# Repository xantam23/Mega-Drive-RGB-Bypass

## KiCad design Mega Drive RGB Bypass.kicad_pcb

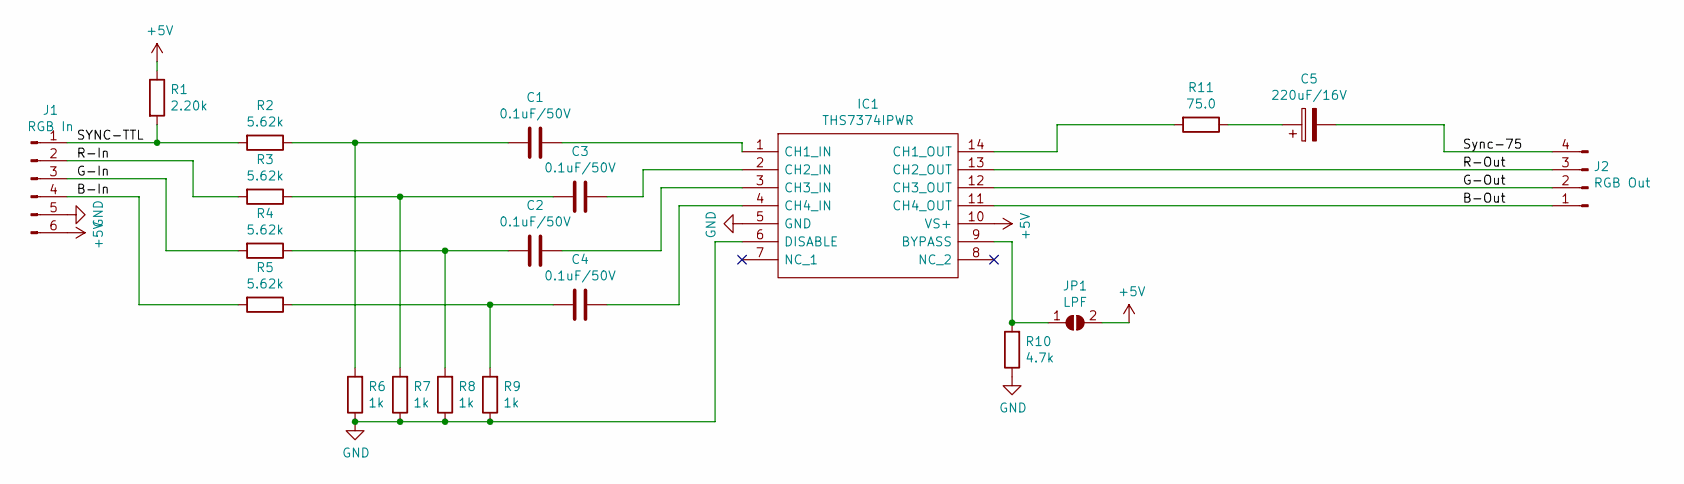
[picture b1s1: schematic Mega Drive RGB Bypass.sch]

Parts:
C1, C2, C3, C4: 0.1uF/50V; C_0805_2012Metric_Pad1.15x1.40mm_HandSolder
C5: 220uF/16V; C_Elec_8x6.2
IC1: THS7374IPWR; SOP65P640X120-14N; Mouser Part Number 595-THS7374IPWR
J1: RGB In; PinHeader_1x06_P2.54mm_Vertical
J2: RGB Out; PinHeader_1x04_P2.54mm_Vertical
JP1: LPF; SolderJumper-2_P1.3mm_Open_TrianglePad1.0x1.5mm
R1: 2.20k; R_0805_2012Metric_Pad1.15x1.40mm_HandSolder
R2, R3, R4, R5: 5.62k; R_0805_2012Metric_Pad1.15x1.40mm_HandSolder
R6, R7, R8, R9: 1k; R_0805_2012Metric_Pad1.15x1.40mm_HandSolder
R10: 4.7k; R_0805_2012Metric_Pad1.15x1.40mm_HandSolder
R11: 75.0; R_0805_2012Metric_Pad1.15x1.40mm_HandSolder

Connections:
+5V: IC1.10 (VS+), J1.6, JP1.2 (B), R1.1
/B-In: J1.4, R5.2
/B-Out: IC1.11 (CH4_OUT), J2.1
/G-In: J1.3, R4.2
/G-Out: IC1.12 (CH3_OUT), J2.2
/R-In: J1.2, R3.2
/R-Out: IC1.13 (CH2_OUT), J2.3
/SYNC-TTL: J1.1, R1.2, R2.2
/Sync-75: C5.2, J2.4
GND: IC1.5 (GND), IC1.6 (DISABLE), J1.5, R6.1, R7.1, R8.1, R9.1, R10.1
unnamed: C1.1, IC1.1 (CH1_IN)
unnamed: C1.2, R2.1, R6.2
unnamed: C2.1, IC1.3 (CH3_IN)
unnamed: C2.2, R4.1, R8.2
unnamed: C3.1, IC1.2 (CH2_IN)
unnamed: C3.2, R3.1, R7.2
unnamed: C4.1, IC1.4 (CH4_IN)
unnamed: C4.2, R5.1, R9.2
unnamed: C5.1, R11.1
unnamed: IC1.9 (BYPASS), JP1.1 (A), R10.2
unnamed: IC1.14 (CH1_OUT), R11.2

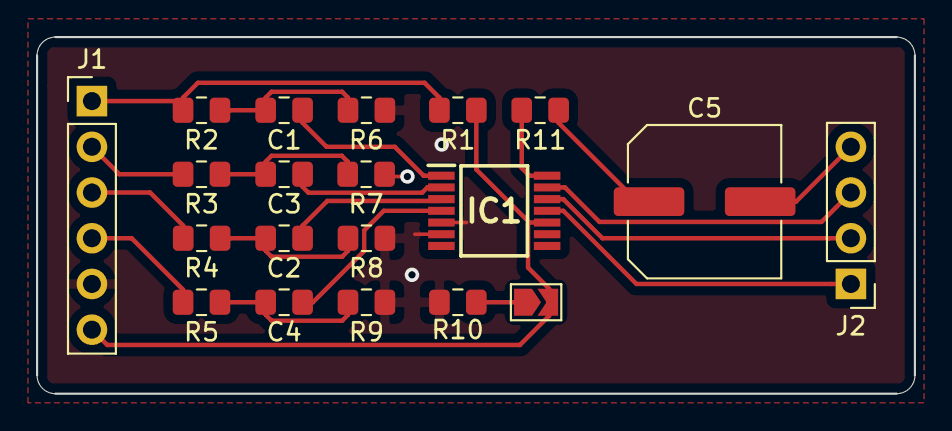
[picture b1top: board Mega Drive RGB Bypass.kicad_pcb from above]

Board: 2 copper layers, 48.8 x 19.8 mm, 20 parts (0 on the bottom side), 21 nets.
